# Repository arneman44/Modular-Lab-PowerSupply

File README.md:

# Project Modular lab powersupply
Arne Van den Broeck

## Desciption
A Modular lab bench powersupply 

### Specs Modules:
* use the eurocard format
* connected via a 40 ribbon cable as a bus 
* its own isolated powersupply 

## Modules:

### Powermodule:
* 0-30V
* 0-3A
* 16bit readout
* 12bit Controll
* Dual powerbus for connecting modules internally

### controller:
* 7inch touchscreen
* Ethernet
* USB host/device
* rotary Encoder

## Future modules:
* DC load
* Waveform generator
* Multimeter
* GPIO

## Files 
All the Kicad files where made using the nightly build of kicad
Version: (5.99.0-9544-g366189b864)

The STM32 project are build with cubeMX with as toolchain makefile.
I use vscode with STM32-for-vscode to build it

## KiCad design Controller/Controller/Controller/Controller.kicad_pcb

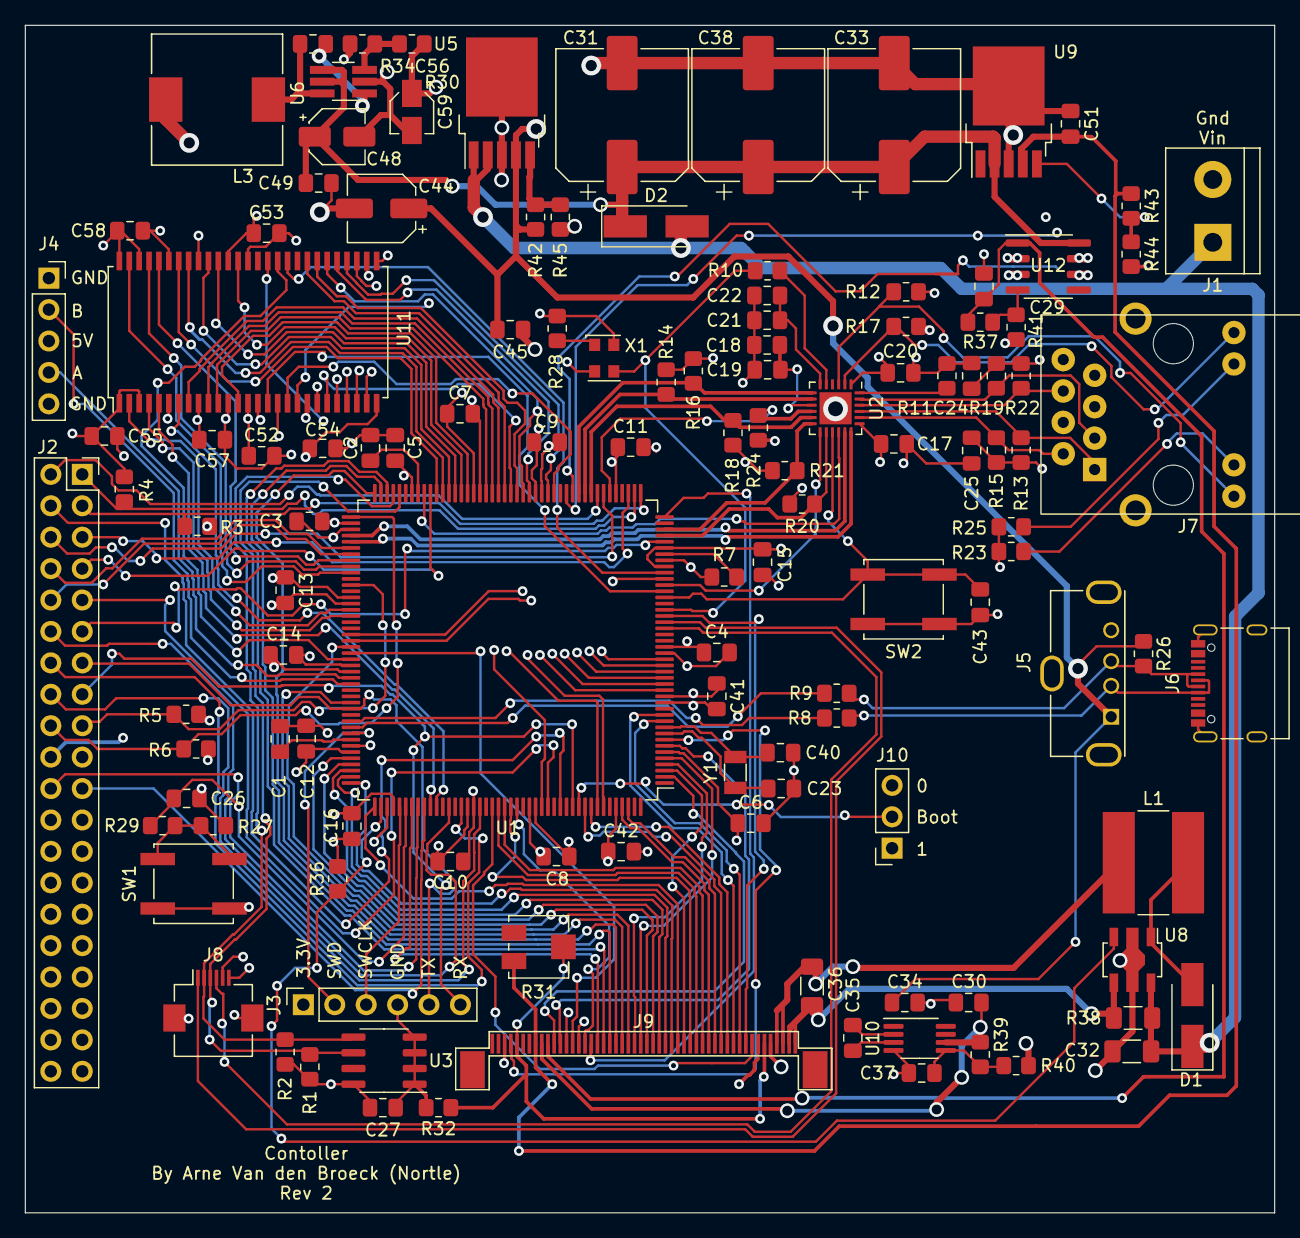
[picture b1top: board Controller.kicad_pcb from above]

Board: 4 copper layers, 101.0 x 96.0 mm, 125 parts (0 on the bottom side), 158 nets.

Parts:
C1, C2: 2.2µF ceramic; C_0805_2012Metric_Pad1.18x1.45mm_HandSolder
C3, C4, C5, C6, C7, C8, C9, C10, C11, C12, C13, C14, C15, C16, C17, C18, C19, C20, C21, C22, C24, C25, C26, C27, C29, C35, C41, C42, C43, C45, C49, C51, C52, C53, C54, C55, C56, C57, C58: 100nF; C_0805_2012Metric_Pad1.18x1.45mm_HandSolder
C23, C40: 4.7pF; C_0805_2012Metric_Pad1.18x1.45mm_HandSolder
C30: 4.7uF; C_0805_2012Metric_Pad1.18x1.45mm_HandSolder
C31, C33, C38: 330uF; CP_Elec_10x10.5
C32: 10µF; C_1206_3216Metric_Pad1.33x1.80mm_HandSolder
C34: 1µF; C_0805_2012Metric_Pad1.18x1.45mm_HandSolder
C36: Optional; C_1206_3216Metric_Pad1.33x1.80mm_HandSolder
C37: 100pF; C_0805_2012Metric_Pad1.18x1.45mm_HandSolder
C44: 100uF; CP_Elec_5x5.4
C48: 3.3uF; CP_Elec_4x5.7
C59: 22uF; CP_Elec_3x5.3
D1, D2: ss34; D_SMA_Handsoldering
J1: Power In; TerminalBlock_bornier-2_P5.08mm
J2: Module Bus; PinSocket_2x20_P2.54mm_Vertical
J3: Programming Header; PinSocket_1x06_P2.54mm_Vertical
J4: Encoder Header; PinSocket_1x05_P2.54mm_Vertical
J5: USB_A; USB_A_Molex_105057_Vertical
J6: USB_C_Receptacle_USB2.0; USB_C_Receptacle_Palconn_UTC16-G
J7: RJ45_Amphenol_RJMG1BD3B8K1ANR; HR913550A
J8: Conn_01x06_MountingPin; Hirose_FH12-6S-0.5SH_1x06-1MP_P0.50mm_Horizontal
J9: Conn_01x50_MountingPin; FPC_50
J10: Boot Select; PinSocket_1x03_P2.54mm_Vertical
L1: 68uH; L_Bourns-SRN8040_8x8.15mm
L3: 15uH; L_10.4x10.4_H4.8
R1, R2, R3, R4, R5, R6, R7, R12, R17, R27, R28, R29, R32, R36: 10Kohm; R_0805_2012Metric_Pad1.20x1.40mm_HandSolder
R8, R9: 22ohm; R_0805_2012Metric_Pad1.20x1.40mm_HandSolder
R10: 100ohm; R_0805_2012Metric_Pad1.20x1.40mm_HandSolder
R11: 12.1Kohm; R_0805_2012Metric_Pad1.20x1.40mm_HandSolder
R13, R15, R19, R22: 50ohm; R_0805_2012Metric_Pad1.20x1.40mm_HandSolder
R14, R16, R18, R20, R24: 4.7Kohm; R_0805_2012Metric_Pad1.20x1.40mm_HandSolder
R21: 1.5Kohm; R_0805_2012Metric_Pad1.20x1.40mm_HandSolder
R23, R25: 330ohm; R_0805_2012Metric_Pad1.20x1.40mm_HandSolder
R26: 47Kohm; R_0805_2012Metric_Pad1.20x1.40mm_HandSolder
R30: 27Kohm; R_0805_2012Metric_Pad1.20x1.40mm_HandSolder
R31: RTRIM; Potentiometer_Bourns_3214J_Horizontal
R34: 62Kohm; R_0805_2012Metric_Pad1.20x1.40mm_HandSolder
R37: 13Kohm; R_0805_2012Metric_Pad1.20x1.40mm_HandSolder
R38: 0.7ohm; R_1206_3216Metric_Pad1.30x1.75mm_HandSolder
R39: 107Kohm; R_0805_2012Metric_Pad1.20x1.40mm_HandSolder
R40: 27.4Kohm; R_0805_2012Metric_Pad1.20x1.40mm_HandSolder
R41: 180Kohm; R_0805_2012Metric_Pad1.20x1.40mm_HandSolder
R42: 12Kohm; R_0805_2012Metric_Pad1.20x1.40mm_HandSolder
R43: 11Kohm; R_0805_2012Metric_Pad1.20x1.40mm_HandSolder
R44: 130Kohm; R_0805_2012Metric_Pad1.20x1.40mm_HandSolder
R45: 68Kohm; R_0805_2012Metric_Pad1.20x1.40mm_HandSolder
SW1, SW2: SW_Push; SW_Push_1P1T_NO_CK_KSC7xxJ
U1: STM32F746IGTx; LQFP-176_24x24mm_P0.5mm
U2: LAN8720A; QFN-24-1EP_4x4mm_P0.5mm_EP2.6x2.6mm
U3: M24C02-WMN; SOIC-8_3.9x4.9mm_P1.27mm
U5, U9: BD00C0AWFP; TO-252-5_TabPin3
U6: LMR50410; TSOT-23-6_HandSoldering
U8: C85037; SOT-89-5
U10: LTC1261L; MSOP-8_3x3mm_P0.65mm
U11: IS42S16400J; TSOP-II-54_22.2x10.16mm_P0.8mm
U12: LM2931-ADJ_soic-8; SOIC-8_3.9x4.9mm_P1.27mm
X1: XO25; Oscillator_SMD_EuroQuartz_XO32-4Pin_3.2x2.5mm
Y1: 32.765Mhz; Crystal_SMD_3215-2Pin_3.2x1.5mm

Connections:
2.9V: J9.6, J9.46, R31.2, R32.1
9.6V: C51.1, J9.43, R31.1, R43.1, U9.4 (VOUT)
18V: C29.1, J9.41, R37.1, U12.1 (VO)
25Mhz: R10.1, U1.29 (PH0), X1.3 (OUT)
+5V: C34.1, C44.1, C45.1, J4.3, J5.1 (VBUS), J6.A4 (VBUS), J6.A9 (VBUS), J6.B4 (VBUS), J6.B9 (VBUS), R26.1, R42.1, U5.4 (VOUT), U10.1 (Vcc)
-6V: C30.1, J9.42, R39.1, U10.6 (OUT)
/RX+: J7.R3 (RD+), R19.2, U2.23 (RXP)
/RX-: J7.R6 (RD-), R22.2, U2.22 (RXN)
/TX+: J7.R1 (TD+), R13.2, U2.21 (TXP)
/TX-: J7.R2 (TD-), R15.2, U2.20 (TXN)
ADDR_LED1: J2.11, U1.40 (PA0)
ADDR_LED2: J2.9, U1.161 (PB3)
ADDR_LED3: J2.7, U1.79 (PB10)
ADDR_LED4: J2.5, U1.47 (PA3)
Backlight: R36.1, U1.134 (PI3), U8.3 (ADJ)
Backlight Anode: C36.1, J9.1, J9.2, R38.2, U8.4 (ISENSE)
Backlight Cathode: C36.2, J9.3, J9.4, L1.2
Boot0: J10.2, U1.166 (BOOT0)
Crystal_32_in: C23.2, U1.9 (PC14), Y1.2
Crystal_32_out: C40.2, U1.10 (PC15), Y1.1
Encoder_A: J4.4, U1.115 (PC6)
Encoder_B: J4.2, U1.116 (PC7)
GND: C1.2, C2.2, C3.2, C4.2, C5.2, C6.2, C7.2, C8.2, C9.2, C10.2, C11.2, C12.2, C13.2, C14.2, C15.2, C16.2, C17.2, C18.2, C19.2, C20.2, C21.2, C22.2, C23.1, C24.2, C25.2, C26.1, C27.2, C29.2, C30.2, C31.2, C32.2, C33.2, C34.2, C37.2, C38.2, C40.1, C41.2, C42.2, C43.2, C44.2, C45.2, C48.2, C49.2, C51.2, C52.2, C53.2, C54.2, C55.2, C57.2, C58.2, C59.2, J1.2, J2.19, J3.4, J4.1, J4.5, J5.4 (GND), J5.5 (Shield), J6.A1 (GND), J6.A12 (GND), J6.B1 (GND), J6.B12 (GND), J6.S1 (SHIELD), J7.13 (SHIELD), J7.R8 (GND), J8.5, J8.MP (MountPin), J9.5, J9.36, J9.38, J9.48, J10.3, R7.2, R11.2, R12.2, R17.2, R23.2, R24.1, R25.2, R27.2, R32.2, R34.2, R36.2, R40.2, R41.2, R44.2, R45.2, SW2.2, U1.14 (VSS), U1.22 (VSS), U1.37 (VSSA), U1.61 (VSS), U1.71 (VSS), U1.90 (VSS), U1.102 (VSS), U1.113 (VSS), U1.126 (VSS), U1.135 (VSS), U1.148 (VSS), U1.158 (VSS), U2.25 (VSS), U3.1 (E0), U3.2 (E1), U3.3 (E2), U3.4 (VSS), U5.3 (GND), U6.2 (GND), U8.2 (GND), U9.3 (GND), U10.4 (GND), U11.6 (VSSQ), U11.12 (VSSQ), U11.28 (VSS), U11.41 (VSS), U11.46 (VSSQ), U11.52 (VSSQ), U11.54 (VSS), U12.2 (GND), U12.3 (GND), U12.6 (GND), U12.7 (GND), X1.2 (GND)
Galv_Enable: J2.22, U1.140 (PC11)
Galv_Interrupt: J2.21, U1.141 (PC12)
I2C2_SCL: J2.3, R3.1, U1.45 (PH4)
I2C2_SDA: J2.1, R4.1, U1.46 (PH5)
I2C3_SCL: J8.3, R1.1, U1.84 (PH7), U3.6 (SCL)
I2C3_SDA: J8.2, R2.1, U1.85 (PH8), U3.5 (SDA)
I2C4_SCL: J2.17, R5.1, U1.100 (PD12)
I2C4_SDA: J2.18, R6.1, U1.89 (PH12)
LCD_B0: J9.19, U1.3 (PE4)
LCD_B1: J9.18, U1.155 (PG12)
LCD_B2: J9.17, U1.153 (PG10)
LCD_B3: J9.16, U1.154 (PG11)
LCD_B4: J9.15, U1.173 (PI4)
LCD_B5: J9.14, U1.174 (PI5)
LCD_B6: J9.13, U1.167 (PB8)
LCD_B7: J9.12, U1.168 (PB9)
LCD_CT_INT: J8.1, U1.27 (PF9)
LCD_CT_RESET: J8.4, U1.26 (PF8)
LCD_DEN: J9.9, U1.28 (PF10)
LCD_DITHB: J9.47, U1.8 (PC13)
LCD_G0: J9.27, U1.4 (PE5)
LCD_G1: J9.26, U1.5 (PE6)
LCD_G2: J9.25, U1.128 (PH13)
LCD_G3: J9.24, U1.129 (PH14)
LCD_G4: J9.23, U1.130 (PH15)
LCD_G5: J9.22, U1.131 (PI0)
LCD_G6: J9.21, U1.132 (PI1)
LCD_G7: J9.20, U1.133 (PI2)
LCD_HSYNC: J9.11, U1.12 (PI10)
LCD_PCLK: J9.37, U1.111 (PG7)
LCD_R0: J9.35, U1.156 (PG13)
LCD_R1: J9.34, U1.44 (PH3)
LCD_R2: J9.33, U1.139 (PC10)
LCD_R3: J9.32, U1.86 (PH9)
LCD_R4: J9.31, U1.87 (PH10)
LCD_R5: J9.30, U1.88 (PH11)
LCD_R6: J9.29, U1.119 (PA8)
LCD_R7: J9.28, U1.110 (PG6)
LCD_SHLR: J9.39, U1.7 (PI8)
LCD_UPDN: J9.40, U1.2 (PE3)
LCD_VDD: C3.1, C4.1, C5.1, C6.1, C7.1, C8.1, C9.1, C10.1, C11.1, C12.1, C13.1, C14.1, C15.1, C16.1, C17.1, C18.1, C19.1, C20.1, C24.1, C25.1, C27.1, C41.1, C42.1, C52.1, C53.1, C54.1, C55.1, C57.1, C58.1, C59.1, J2.20, J3.1, J7.R4 (TCT), J7.R5 (RCT), J8.6, J9.7, J10.1, L3.2, R1.2, R2.2, R3.2, R4.2, R5.2, R6.2, R13.1, R14.1, R15.1, R16.1, R18.1, R19.1, R20.1, R21.1, R22.1, R28.1, R30.1, SW1.1, U1.6 (VBAT), U1.15 (VDD), U1.23 (VDD), U1.36 (VDD), U1.39 (VDDA), U1.49 (VDD), U1.62 (VDD), U1.72 (VDD), U1.82 (VDD), U1.91 (VDD), U1.103 (VDD), U1.114 (VDDUSB), U1.127 (VDD), U1.136 (VDD), U1.149 (VDD), U1.159 (VDD), U1.172 (VDD), U2.1 (VDD2A), U2.9 (VDDIO), U2.19 (VDD1A), U3.8 (VCC), U11.1 (VDD), U11.3 (VDDQ), U11.9 (VDDQ), U11.14 (VDD), U11.27 (VDD), U11.43 (VDDQ), U11.49 (VDDQ), X1.4 (V+)
LCD_VSYNC: J9.10, U1.11 (PI9)
LDC_MODE: J9.8, U1.152 (PG9)
unnamed: C21.1, C22.1, U2.6 (VDDCR)
unnamed: C35.1, U10.2 (C1+)
unnamed: C35.2, U10.3 (C1-)
unnamed: C37.1, R39.2, R40.1, U10.5 (ADJ)
unnamed: C56.1, L3.1, U6.6 (SW)
unnamed: C56.2, U6.1 (CB)
unnamed: D1.2 (A), L1.1, U8.1 (LX)
unnamed: J7.L1 (LEDY_A), R17.1, U2.2 (LED2/nINTSEL)
unnamed: J7.L2 (LEDY_K), R25.1
unnamed: J7.L3 (LEDG_K), R23.1
unnamed: J7.L4 (LEDG_A), R12.1, U2.3 (LED1/REGOFF)
unnamed: R7.1, U1.38 (VREF+)
unnamed: R8.1, U1.122 (PA11)
unnamed: R9.1, U1.123 (PA12)
unnamed: R10.2, U2.5 (XTAL1/CLKIN)
unnamed: R11.1, U2.24 (RBIAS)
unnamed: R27.1, R29.2, SW1.2
unnamed: R28.2, X1.1 (EN)
unnamed: R30.2, R34.1, U6.3 (FB)
unnamed: R37.2, R41.1, U12.4 (ADJ)
unnamed: R42.2, R45.1, U5.5 (ADJ)
unnamed: R43.2, R44.1, U9.5 (ADJ)
RESET: C43.1, SW2.1, U1.31 (NRST), U2.15 (RST)
RMII_CRS_DV: R18.2, U1.53 (PA7), U2.11 (CRS_DV/MODE2)
RMII_MDC: U1.33 (PC1), U2.13 (MDC)
RMII_MDIO: R21.2, U1.42 (PA2), U2.12 (MDIO)
RMII_REF_CLK: R20.2, U1.41 (PA1), U2.14 (INT/REFCLKO)
RMII_RXD+: R16.2, U1.55 (PC5), U2.7 (RXD1/MODE1)
RMII_RXD-: R14.2, U1.54 (PC4), U2.8 (RXD0/MODE0)
RMII_RXER: R24.2, U1.50 (PA4), U2.10 (RXER/PHYAD0)
RMII_TXD+: U1.93 (PB13), U2.18 (TXD1)
RMII_TXD-: U1.92 (PB12), U2.17 (TXD0)
RMII_TXEN: U1.80 (PB11), U2.16 (TXEN)
SDRAM_A0: U1.16 (PF0), U11.23 (A0)
SDRAM_A1: U1.17 (PF1), U11.24 (A1)
SDRAM_A2: U1.18 (PF2), U11.25 (A2)
SDRAM_A3: U1.19 (PF3), U11.26 (A3)
SDRAM_A4: U1.20 (PF4), U11.29 (A4)
SDRAM_A5: U1.21 (PF5), U11.30 (A5)
SDRAM_A6: U1.60 (PF12), U11.31 (A6)
SDRAM_A7: U1.63 (PF13), U11.32 (A7)
SDRAM_A8: U1.64 (PF14), U11.33 (A8)
SDRAM_A9: U1.65 (PF15), U11.34 (A9)
SDRAM_A10: U1.66 (PG0), U11.22 (A10)
SDRAM_A11: U1.67 (PG1), U11.35 (A11)
SDRAM_BA0: U1.108 (PG4), U11.20 (BA0)
SDRAM_BA1: U1.109 (PG5), U11.21 (BA1)
SDRAM_D0: U1.104 (PD14), U11.2 (DQ0)
SDRAM_D1: U1.105 (PD15), U11.4 (DQ1)
SDRAM_D2: U1.142 (PD0), U11.5 (DQ2)
SDRAM_D3: U1.143 (PD1), U11.7 (DQ3)
SDRAM_D4: U1.68 (PE7), U11.8 (DQ4)
SDRAM_D5: U1.69 (PE8), U11.10 (DQ5)
SDRAM_D6: U1.70 (PE9), U11.11 (DQ6)
SDRAM_D7: U1.73 (PE10), U11.13 (DQ7)
SDRAM_D8: U1.74 (PE11), U11.42 (DQ8)
SDRAM_D9: U1.75 (PE12), U11.44 (DQ9)
SDRAM_D10: U1.76 (PE13), U11.45 (DQ10)
SDRAM_D11: U1.77 (PE14), U11.47 (DQ11)
SDRAM_D12: U1.78 (PE15), U11.48 (DQ12)
SDRAM_D13: U1.96 (PD8), U11.50 (DQ13)
SDRAM_D14: U1.97 (PD9), U11.51 (DQ14)
SDRAM_D15: U1.98 (PD10), U11.53 (DQ15)
SDRAM_NBL0: U1.169 (PE0), U11.15 (DQML)
SDRAM_NBL1: U1.170 (PE1), U11.39 (DQMH)
SDRAM_SDCKE0: U1.35 (PC3), U11.37 (CKE)
SDRAM_SDCLK: U1.112 (PG8), U11.38 (CLK)
SDRAM_SDNCAS: U1.160 (PG15), U11.17 (~CAS~)
SDRAM_SDNE0: U1.34 (PC2), U11.19 (~CS~)
SDRAM_SDNRAS: U1.59 (PF11), U11.18 (~RAS~)
SDRAM_SDNWE: U1.32 (PC0), U11.16 (~WE~)
SPI1_MISO: J2.2, U1.52 (PA6)
SPI1_MOSI: J2.4, U1.163 (PB5)
SPI1_SCK: J2.6, U1.51 (PA5)
SPI2_MISO: J2.8, U1.94 (PB14)
SPI2_MOSI: J2.10, U1.95 (PB15)
SPI2_SCK: J2.12, U1.145 (PD3)
SWCLK: J3.3, U1.137 (PA14)
SWD: J3.2, U1.124 (PA13)
UART_RX1: J2.15, J3.6, U1.165 (PB7)
UART_RX2: J2.16, U1.150 (PD6)
UART_TX1: J2.13, J3.5, U1.120 (PA9)
UART_TX2: J2.14, U1.147 (PD5)
USB_OTG_D+: J5.3 (D+), J6.A6 (D+), J6.B6 (D+), R9.2, R26.2
USB_OTG_D-: J5.2 (D-), J6.A7 (D-), J6.B7 (D-), R8.2
USER_BTN: C26.2, R29.1, U1.138 (PA15)
VLCD: C31.1, C33.1, C38.1, C48.1, C49.1, D2.1 (K), U6.4 (EN), U6.5 (Vin), U9.2 (VIN), U12.8 (VI)
Vcap1: C2.1, U1.81 (VCAP_1)
Vcap2: C1.1, U1.125 (VCAP_2)
Vin: C32.1, D1.1 (K), D2.2 (A), J1.1, R38.1, U5.1 (EN), U5.2 (VIN), U8.5 (VIN)
Virt-Bus1: J2.33, J2.34, J2.35, J2.36, J2.37, J2.38, J2.39, J2.40
Virt-Bus2: J2.25, J2.26, J2.27, J2.28, J2.29, J2.30, J2.31, J2.32

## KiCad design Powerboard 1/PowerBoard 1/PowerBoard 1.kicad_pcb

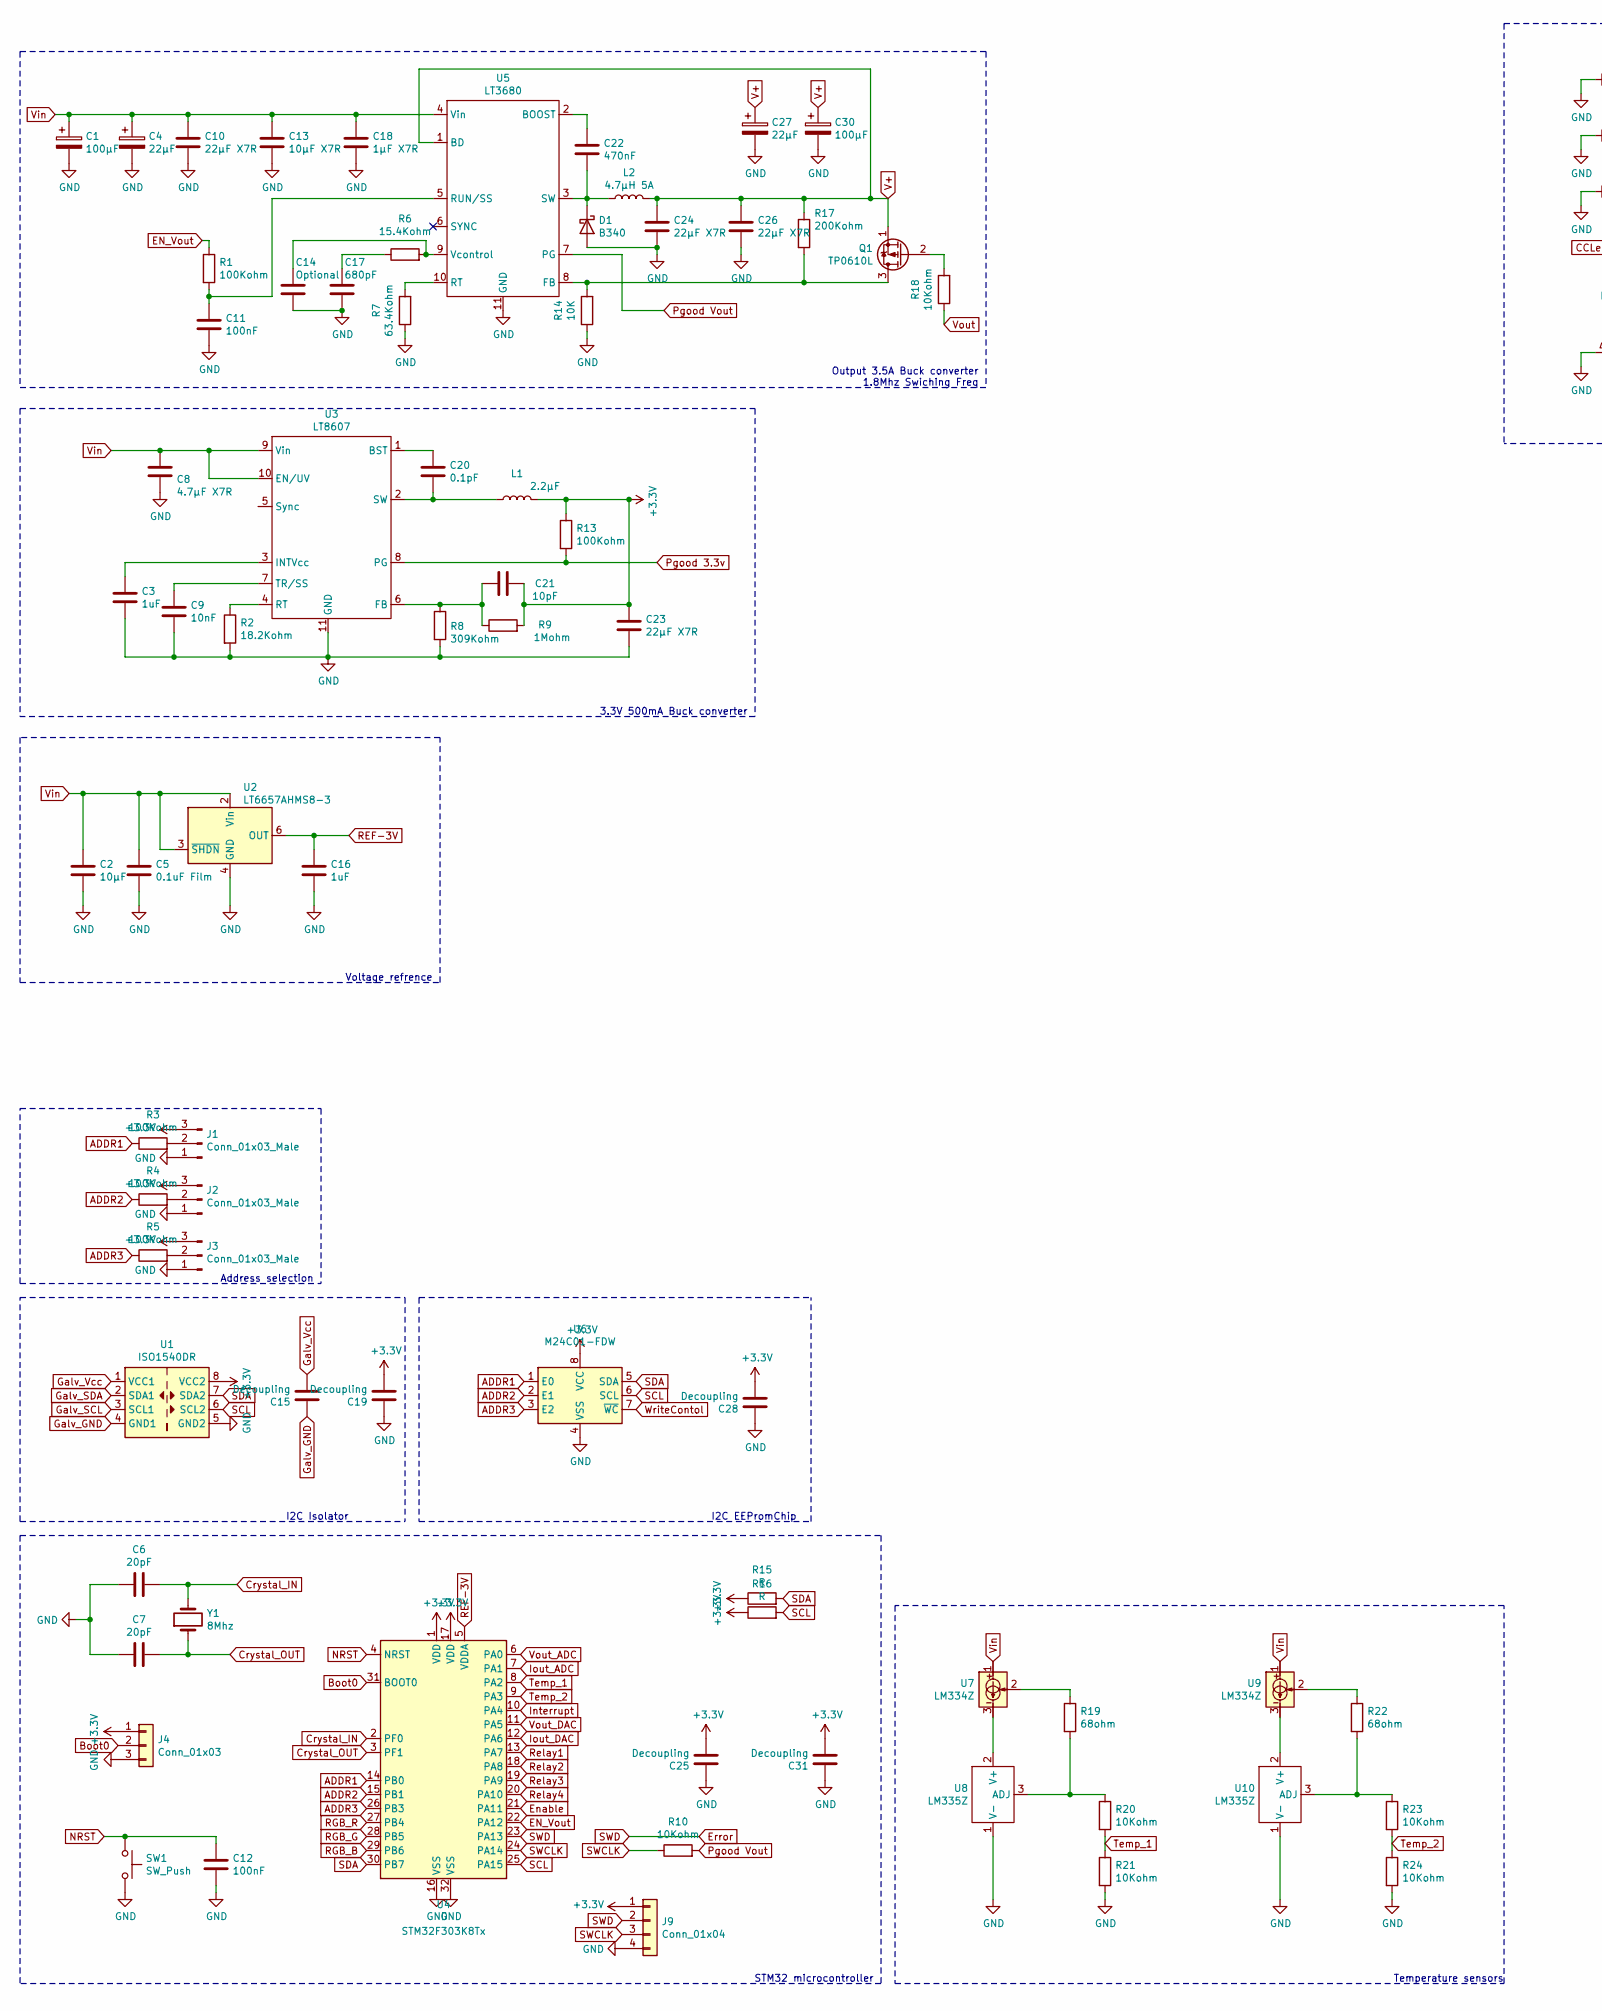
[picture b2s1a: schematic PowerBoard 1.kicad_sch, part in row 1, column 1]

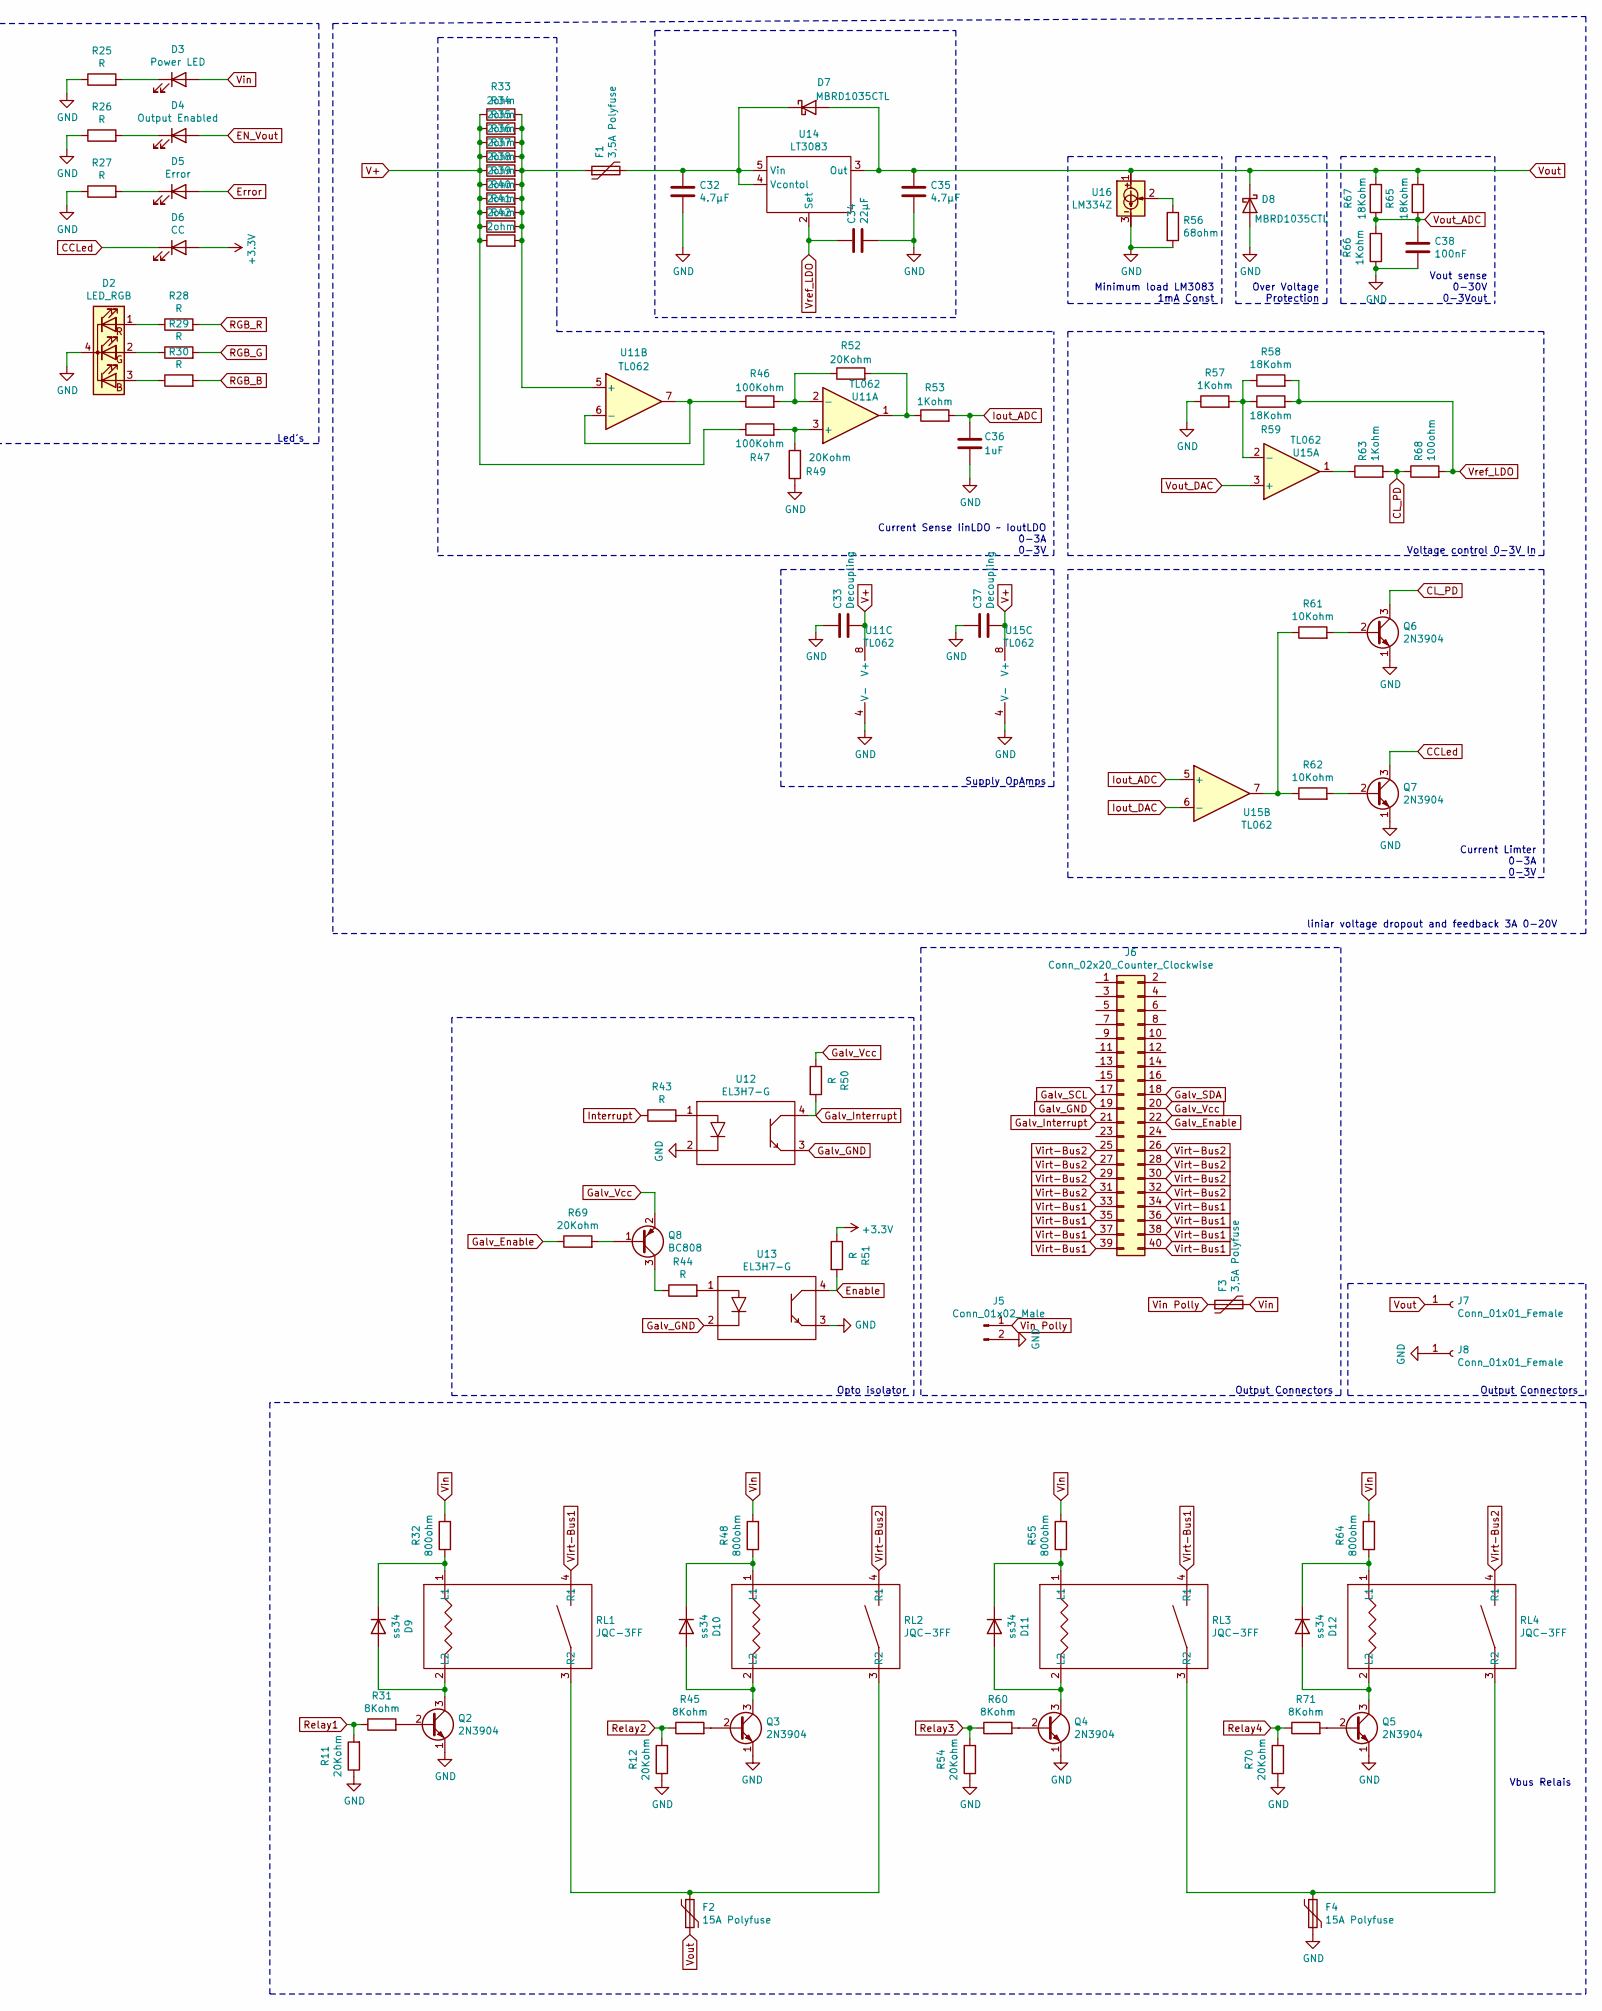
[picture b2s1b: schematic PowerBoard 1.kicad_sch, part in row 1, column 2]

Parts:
C1, C30: 100µF; C_Elec_8x10.2
C2: 10µF; C_0805_2012Metric_Pad1.18x1.45mm_HandSolder
C3, C16, C36: 1uF; C_0805_2012Metric_Pad1.18x1.45mm_HandSolder
C4, C27: 22µF; C_Elec_6.3x5.4
C5: 0.1uF Film; C_0805_2012Metric_Pad1.18x1.45mm_HandSolder
C6, C7: 20pF; C_0805_2012Metric_Pad1.18x1.45mm_HandSolder
C8: 4.7µF X7R; C_1206_3216Metric_Pad1.33x1.80mm_HandSolder
C9: 10nF; C_0805_2012Metric_Pad1.18x1.45mm_HandSolder
C10, C23, C24, C26: 22µF X7R; C_2220_5650Metric_Pad1.97x5.40mm_HandSolder
C11, C12, C38: 100nF; C_0805_2012Metric_Pad1.18x1.45mm_HandSolder
C13: 10µF X7R; C_1206_3216Metric_Pad1.33x1.80mm_HandSolder
C14: Optional; C_0805_2012Metric_Pad1.18x1.45mm_HandSolder
C15, C19, C25, C28, C31, C33, C37: Decoupling; C_0805_2012Metric_Pad1.18x1.45mm_HandSolder
C17: 680pF; C_0805_2012Metric_Pad1.18x1.45mm_HandSolder
C18: 1µF X7R; C_0805_2012Metric_Pad1.18x1.45mm_HandSolder
C20: 0.1pF; C_0603_1608Metric_Pad1.08x0.95mm_HandSolder
C21: 10pF; C_0805_2012Metric_Pad1.18x1.45mm_HandSolder
C22: 470nF; C_0805_2012Metric_Pad1.18x1.45mm_HandSolder
C32, C35: 4.7µF; C_0805_2012Metric_Pad1.18x1.45mm_HandSolder
C34: 22µF; C_0805_2012Metric_Pad1.18x1.45mm_HandSolder
D1: B340; D_SMA_Handsoldering
D2: LED_RGB; LED_D5.0mm-4_RGB_Wide_Pins
D3: Power LED; LED_D5.0mm
D4: Output Enabled; LED_D5.0mm
D5: Error; LED_D5.0mm
D6: CC; LED_D5.0mm
D7, D8: MBRD1035CTL; TO-252-2
D9, D10, D11, D12: ss34; D_SMA_Handsoldering; LCSC C83961
F1, F3: 3,5A Polyfuse; Fuse_1206_3216Metric_Pad1.42x1.75mm_HandSolder
F2, F4: 15A Polyfuse; Fuse_1812_4532Metric_Pad1.30x3.40mm_HandSolder
J1, J2, J3: Conn_01x03_Male; PinSocket_1x03_P2.54mm_Vertical
J4: Conn_01x03; PinSocket_1x03_P2.54mm_Vertical
J5: Conn_01x02_Male; TerminalBlock_bornier-2_P5.08mm
J6: Conn_02x20_Counter_Clockwise; PinSocket_2x20_P2.54mm_Vertical
J7, J8: Conn_01x01_Female; SolderWirePad_1x01_SMD_5x10mm
J9: Conn_01x04; PinSocket_1x04_P2.54mm_Vertical
L1: 2.2µF; L_Wuerth_MAPI-3020
L2: 4.7µH 5A; L_7.3x7.3_H3.5
Q1: TP0610L; SOT-23
Q2, Q3, Q4, Q5, Q6, Q7: 2N3904; SOT-23
Q8: BC808; SOT-23
R1, R3, R4, R5, R13, R46, R47: 100Kohm; R_0805_2012Metric_Pad1.20x1.40mm_HandSolder
R2: 18.2Kohm; R_0805_2012Metric_Pad1.20x1.40mm_HandSolder
R6: 15.4Kohm; R_0805_2012Metric_Pad1.20x1.40mm_HandSolder
R7: 63.4Kohm; R_0805_2012Metric_Pad1.20x1.40mm_HandSolder
R8: 309Kohm; R_0805_2012Metric_Pad1.20x1.40mm_HandSolder
R9: 1Mohm; R_0805_2012Metric_Pad1.20x1.40mm_HandSolder
R10, R18, R20, R21, R23, R24, R61, R62: 10Kohm; R_0805_2012Metric_Pad1.20x1.40mm_HandSolder
R11, R12, R49, R52, R54, R69, R70: 20Kohm; R_0805_2012Metric_Pad1.20x1.40mm_HandSolder
R14: 10K; R_0805_2012Metric_Pad1.20x1.40mm_HandSolder
R15, R16, R25, R26, R27, R28, R29, R30, R43, R44, R50, R51: R; R_0805_2012Metric_Pad1.20x1.40mm_HandSolder
R17: 200Kohm; R_0805_2012Metric_Pad1.20x1.40mm_HandSolder
R19, R22, R56: 68ohm; R_0805_2012Metric_Pad1.20x1.40mm_HandSolder
R31, R45, R60, R71: 8Kohm; R_0805_2012Metric_Pad1.20x1.40mm_HandSolder
R32, R48, R55, R64: 800ohm; R_0805_2012Metric_Pad1.20x1.40mm_HandSolder
R33, R34, R35, R36, R37, R38, R39, R40, R41, R42: 2ohm; R_0805_2012Metric_Pad1.20x1.40mm_HandSolder
R53, R57, R63, R66: 1Kohm; R_0805_2012Metric_Pad1.20x1.40mm_HandSolder
R58, R59, R65, R67: 18Kohm; R_0805_2012Metric_Pad1.20x1.40mm_HandSolder
R68: 100ohm; R_0805_2012Metric_Pad1.20x1.40mm_HandSolder
RL1, RL2, RL3, RL4: JQC-3FF
SW1: SW_Push; SW_Push_1P1T_NO_CK_KSC7xxJ
U1: ISO1540DR; SOIC-8_3.9x4.9mm_P1.27mm
U2: LT6657AHMS8-3; MSOP-8_3x3mm_P0.65mm
U3: LT8607; MSOP-10_handsolder
U4: STM32F303K8Tx; LQFP-32_7x7mm_P0.8mm
U5: LT3680; MSOP-10_handsolder
U6: M24C01-FDW; TSSOP-8_4.4x3mm_P0.65mm
U7, U9, U16: LM334Z; TO-92_Inline
U8, U10: LM335Z; TO-92_Inline
U11, U15: TL062; SOIC-8_3.9x4.9mm_P1.27mm
U12, U13: EL3H7-G; SOP-4_4.4x2.6mm_P1.27mm
U14: LT3083; TO-220-5_Horizontal_TabDown
Y1: 8Mhz; Crystal_SMD_HC49-SD_HandSoldering

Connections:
+3V3: C19.1, C21.2, C23.1, C25.1, C28.1, C31.1, D6.2 (A), J1.3, J2.3, J3.3, J4.1, J9.1, L1.2, R9.2, R13.1, R15.1, R16.1, R51.1, U1.8 (VCC2), U4.1 (VDD), U4.17 (VDD), U6.8 (VCC)
ADDR1: R3.1, U4.14 (PB0), U6.1 (E0)
ADDR2: R4.1, U4.15 (PB1), U6.2 (E1)
ADDR3: R5.1, U4.26 (PB3), U6.3 (E2)
Boot0: J4.2, U4.31 (BOOT0)
CCLed: D6.1 (K), Q7.3 (C)
CL_PD: Q6.3 (C), R63.2, R68.1
Crystal_IN: C6.2, U4.2 (PF0), Y1.2
Crystal_OUT: C7.2, U4.3 (PF1), Y1.1
EN_Vout: D4.2 (A), R1.1, U4.22 (PA12)
Enable: R51.2, U4.21 (PA11), U13.4
Error: D5.2 (A), J9.2, U4.23 (PA13)
GND: C1.2, C2.2, C3.2, C4.2, C5.2, C6.1, C7.1, C8.2, C9.2, C10.2, C11.2, C12.2, C13.2, C14.2, C16.2, C17.2, C18.2, C19.2, C23.2, C24.2, C25.2, C26.2, C27.2, C28.2, C30.2, C31.2, C32.2, C33.2, C34.2, C35.2, C36.1, C37.2, C38.1, D1.2 (A), D2.4 (K), D8.2 (A), F4.2, J1.1, J2.1, J3.1, J4.3, J5.2, J8.1, J9.4, Q2.1 (E), Q3.1 (E), Q4.1 (E), Q5.1 (E), Q6.1 (E), Q7.1 (E), R2.2, R7.1, R8.2, R11.1, R12.1, R14.1, R21.2, R24.2, R25.1, R26.1, R27.1, R49.1, R54.1, R56.2, R57.1, R66.1, R70.1, SW1.2, U1.5 (GND2), U2.4 (GND), U3.11 (GND), U4.16 (VSS), U4.32 (VSS), U5.11 (GND), U6.4 (VSS), U8.1 (V-), U10.1 (V-), U11.4 (V-), U12.2, U13.3, U15.4 (V-), U16.3
Galv_Enable: J6.22, R69.1
Galv_GND: C15.2, J6.19, U1.4 (GND1), U12.3, U13.2
Galv_Interrupt: J6.21, R50.2, U12.4
Galv_SCL: J6.17, U1.3 (SCL1)
Galv_SDA: J6.18, U1.2 (SDA1)
Galv_Vcc: C15.1, J6.20, Q8.2 (E), R50.1, U1.1 (VCC1)
Interrupt: R43.1, U4.10 (PA4)
NRST: C12.1, SW1.1, U4.4 (NRST)
unnamed: C3.1, U3.3 (INTVcc)
unnamed: C9.1, U3.7 (TR/SS)
unnamed: C11.1, R1.2, U5.5 (RUN/SS)
unnamed: C14.1, R6.2, U5.9 (Vcontrol)
unnamed: C17.1, R6.1
unnamed: C20.1, U3.1 (BST)
unnamed: C20.2, L1.1, U3.2 (SW)
unnamed: C21.1, R8.1, R9.1, U3.6 (FB)
unnamed: C22.1, U5.2 (BOOST)
unnamed: C22.2, D1.1 (K), L2.1, U5.3 (SW)
unnamed: C32.1, D7.1 (K), F1.2, U14.4 (Vcontol), U14.5 (Vin)
unnamed: D2.1 (RA), R28.1
unnamed: D2.2 (GA), R29.1
unnamed: D2.3 (BA), R30.1
unnamed: D3.1 (K), R25.2
unnamed: D4.1 (K), R26.2
unnamed: D5.1 (K), R27.2
unnamed: D9.1 (K), R32.1, RL1.1 (L1)
unnamed: D9.2 (A), Q2.3 (C), RL1.2 (L2)
unnamed: D10.1 (K), R48.1, RL2.1 (L1)
unnamed: D10.2 (A), Q3.3 (C), RL2.2 (L2)
unnamed: D11.1 (K), R55.1, RL3.1 (L1)
unnamed: D11.2 (A), Q4.3 (C), RL3.2 (L2)
unnamed: D12.1 (K), R64.1, RL4.1 (L1)
unnamed: D12.2 (A), Q5.3 (C), RL4.2 (L2)
unnamed: F1.1, R33.2, R34.2, R35.2, R36.2, R37.2, R38.2, R39.2, R40.2, R41.2, R42.2, U11.5 (+)
unnamed: F2.1, RL1.3 (R2), RL2.3 (R2)
unnamed: F4.1, RL3.3 (R2), RL4.3 (R2)
unnamed: J1.2, R3.2
unnamed: J2.2, R4.2
unnamed: J3.2, R5.2
unnamed: Q1.2 (G), R18.2
unnamed: Q1.3 (D), R14.2, R17.2, U5.8 (FB)
unnamed: Q2.2 (B), R31.2
unnamed: Q3.2 (B), R45.2
unnamed: Q4.2 (B), R60.2
unnamed: Q5.2 (B), R71.2
unnamed: Q6.2 (B), R61.2
unnamed: Q7.2 (B), R62.2
unnamed: Q8.1 (B), R69.2
unnamed: Q8.3 (C), R44.1
unnamed: R2.1, U3.4 (RT)
unnamed: R7.2, U5.10 (RT)
unnamed: R19.1, U7.2
unnamed: R19.2, R20.1, U8.3 (ADJ)
unnamed: R22.1, U9.2
unnamed: R22.2, R23.1, U10.3 (ADJ)
unnamed: R43.2, U12.1
unnamed: R44.2, U13.1
unnamed: R46.1, U11.6 (-), U11.7
unnamed: R46.2, R52.1, U11.2 (-)
unnamed 72: R47.2, R49.2, U11.3 (+); also elsewhere on the board
unnamed: R52.2, R53.1, U11.1
unnamed: R56.1, U16.2
unnamed: R57.2, R58.1, R59.1, U15.2 (-)
unnamed: R61.1, R62.1, U15.7
unnamed: R63.1, U15.1
unnamed: U7.3, U8.2 (V+)
unnamed: U9.3, U10.2 (V+)
Pgood 3.3v: R13.2, U3.8 (PG)
Pgood Vout: R10.2, U5.7 (PG)
REF-3V: C16.1, U2.6 (OUT), U4.5 (VDDA)
RGB_B: R30.2, U4.29 (PB6)
RGB_G: R29.2, U4.28 (PB5)
RGB_R: R28.2, U4.27 (PB4)
Relay1: R11.2, R31.1, U4.13 (PA7)
Relay2: R12.2, R45.1, U4.18 (PA8)
Relay3: R54.2, R60.1, U4.19 (PA9)
Relay4: R70.2, R71.1, U4.20 (PA10)
SCL: R16.2, U1.6 (SCL2), U4.25 (PA15), U6.6 (SCL)
SDA: R15.2, U1.7 (SDA2), U4.30 (PB7), U6.5 (SDA)
SWCLK: J9.3, R10.1, U4.24 (PA14)
Temp_1: R20.2, R21.1, U4.8 (PA2)
Temp_2: R23.2, R24.1, U4.9 (PA3)
V+: C24.1, C26.1, C27.1, C30.1, C33.1, C37.1, L2.2, Q1.1 (S), R17.1, R33.1, R34.1, R35.1, R36.1, R37.1, R38.1, R39.1, R40.1, R41.1, R42.1, R47.1, U5.1 (BD), U11.8 (V+), U15.8 (V+); also elsewhere on the board
Vin: C1.1, C2.1, C4.1, C5.1, C8.1, C10.1, C13.1, C18.1, D3.2 (A), F3.2, R32.2, R48.2, R55.2, R64.2, U2.2 (Vin), U2.3 (~SHDN), U3.9 (Vin), U3.10 (EN/UV), U5.4 (Vin), U7.1, U9.1
Vin Polly: F3.1, J5.1
Virt-Bus1: J6.33, J6.34, J6.35, J6.36, J6.37, J6.38, J6.39, J6.40, RL1.4 (R1), RL3.4 (R1)
Virt-Bus2: J6.25, J6.26, J6.27, J6.28, J6.29, J6.30, J6.31, J6.32, RL2.4 (R1), RL4.4 (R1)
Vout: C35.1, D7.2 (A), D8.1 (K), F2.2, J7.1, R18.1, R65.2, R67.2, U14.3 (Out), U16.1
Vout_ADC: C38.2, R65.1, R66.2, R67.1, U4.6 (PA0)
Vout_DAC: U4.11 (PA5), U15.3 (+)
Vref_LDO: C34.1, R58.2, R59.2, R68.2, U14.2 (Set)

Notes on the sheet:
Address selection
I2C Isolator
Voltage refrence
3.3V 500mA Buck converter
I2C EEPromChip
STM32 microcontroller
Output 3.5A Buck converter 1.8Mhz Swiching Freq
Temperature sensors
Led's
Opto isolator
Current Sense IinLDO ~~ IoutLDO 0-3A 0-3V
Supply OpAmps
Minimum load LM3083 1mA Const
Over Voltage Protection
Output Connectors
Vout sense 0-30V 0-3Vout
Voltage control 0-3V In
Current Limter 0-3A 0-3V
liniar voltage dropout and feedback 3A 0-20V
Vbus Relais

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
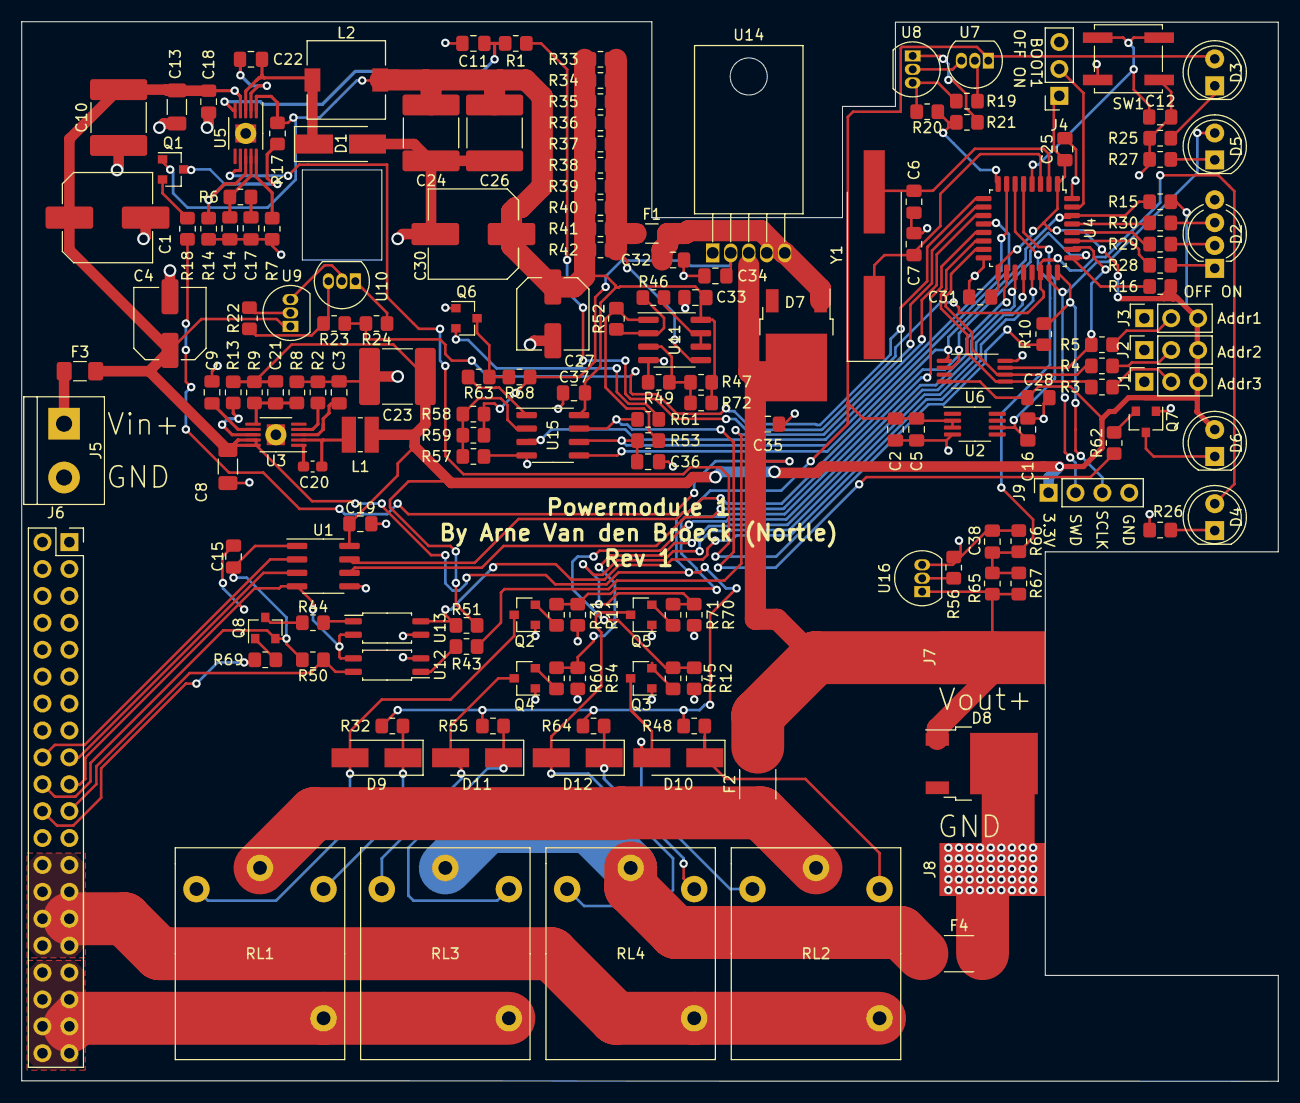
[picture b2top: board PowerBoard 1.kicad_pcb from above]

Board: 2 copper layers, 118.7 x 100.0 mm, 166 parts (0 on the bottom side), 106 nets.

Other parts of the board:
R72: 2Kohm; R_0805_2012Metric_Pad1.20x1.40mm_HandSolder

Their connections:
unnamed 72: R72.2; also elsewhere on the board
V+: R72.1; also elsewhere on the board

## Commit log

2021-03-07 Power supply module REV 1
    Adding the power supply module to the GIT
2021-03-07 Lcd Board REV 1
    Adding Lcd Board to the GIT
2021-03-07 Add gitignore
2021-03-07 Removed Backup files
2021-03-07 added Docs folder
2021-03-07 Added Readme
2021-03-09 changed LCDboard to Controller
2021-03-11 Rev 1 LCD contoller board
2021-03-14 contoller and contoller front Rev 1
2021-03-14 updated powerboard front to remove copper
2021-03-14 added some gerbers
2021-03-16 ReV 2 of the contoller Board
2021-03-16 Updated Gerbers
2021-03-16 Add TouchGFX project
2021-04-26 Rev 3 Pcb's
2021-05-04 working hardware config for contoller
2021-05-24 Final Version Tested
